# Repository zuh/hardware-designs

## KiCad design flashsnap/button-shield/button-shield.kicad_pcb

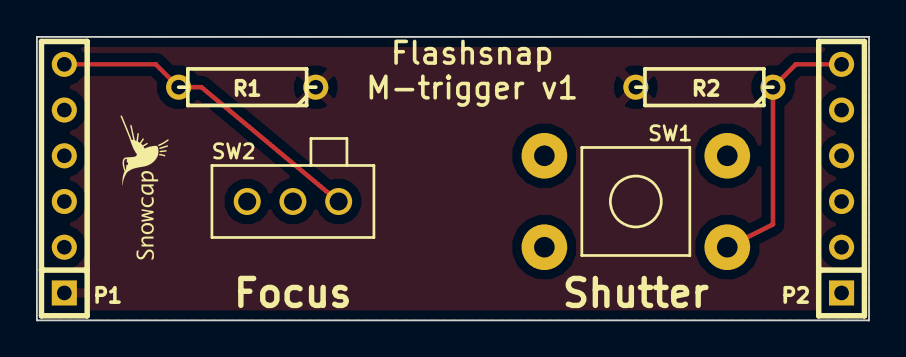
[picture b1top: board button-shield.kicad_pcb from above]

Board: 2 copper layers, 46.2 x 15.7 mm, 7 parts (0 on the bottom side), 4 nets.

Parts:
P1, P2: CONN_6; SIL-6
R1, R2: R; R3
SW1: SW_PUSH; SW_PUSH_6MM
SW2: DUAL_SWITCH_INV; SLIDE_SWITCH
VAL: REF; LOGO_SMALL_SNOWCAP_FRONT

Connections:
unnamed: P1.6, R1.2, SW2.1
unnamed: P2.6, R2.1, SW1.2
unnamed: P1.2, SW1.1, SW2.2
unnamed: P1.1, R1.1, R2.2

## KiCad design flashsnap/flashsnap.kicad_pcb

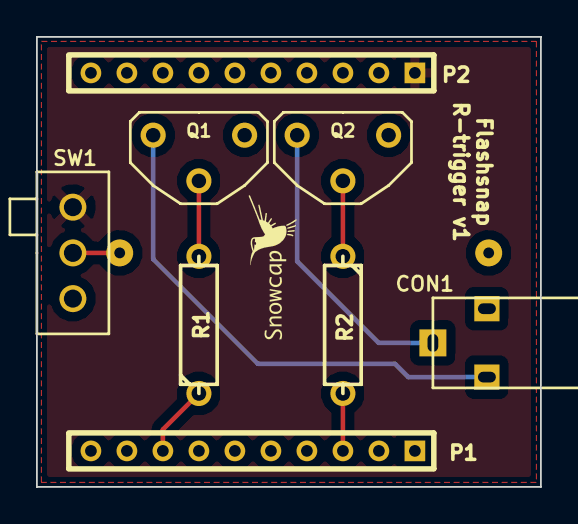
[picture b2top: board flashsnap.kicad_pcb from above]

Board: 2 copper layers, 28.0 x 25.0 mm, 10 parts (1 on the bottom side), 9 nets.

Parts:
BT1: BATTERY; BX2032
CON1: BARREL_JACK; SJ2.5PC
P1, P2: CONN_10; CONN-10-2MM
Q1, Q2: NPN; TO92PN-LARGE
R1, R2: R; R3
SW1: SWITCH_INV; SLIDE_SWITCH
VAL: REF; LOGO_SMALL_SNOWCAP_FRONT

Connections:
unnamed: P2.1, SW1.1
unnamed: BT1.2, CON1.1, P2.10, Q1.1, Q2.1
unnamed: BT1.1, SW1.2
unnamed: Q1.2, R1.2
unnamed: P1.3, R2.2
unnamed: Q2.2, R2.1
unnamed: CON1.3, Q2.3
unnamed: CON1.2, Q1.3
unnamed: P1.8, R1.1

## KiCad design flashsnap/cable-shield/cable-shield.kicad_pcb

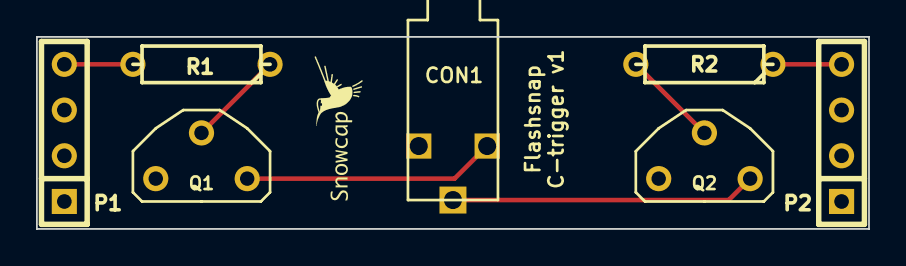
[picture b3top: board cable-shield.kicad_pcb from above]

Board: 2 copper layers, 46.2 x 10.7 mm, 8 parts (0 on the bottom side), 7 nets.

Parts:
CON1: BARREL_JACK; SJ2.5PC
P1, P2: CONN_4; SIL-4
Q1, Q2: NPN; TO92PN-LARGE
R1, R2: R; R3
VAL: REF; LOGO_SMALL_SNOWCAP_FRONT

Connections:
unnamed: CON1.1, P1.2, Q1.1, Q2.1
unnamed: CON1.2, Q1.3
unnamed: CON1.3, Q2.3
unnamed: Q2.2, R2.2
unnamed: Q1.2, R1.1
unnamed: P1.4, R1.2
unnamed: P2.4, R2.1

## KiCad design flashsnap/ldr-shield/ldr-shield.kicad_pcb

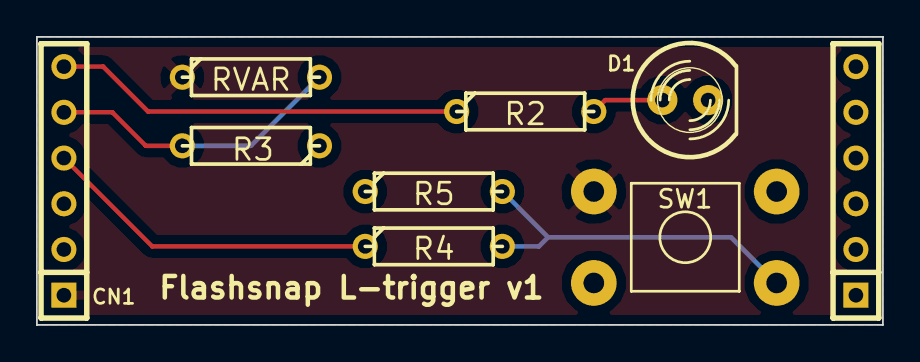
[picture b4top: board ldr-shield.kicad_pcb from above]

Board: 2 copper layers, 47.0 x 16.0 mm, 9 parts (0 on the bottom side), 7 nets.

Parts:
CN1, CN2: CN_6; SIL-6
D1: LED; LED-5MM
R1: RVAR; R3
R2, R3, R4, R5: R; R3
SW1: SW_PUSH; SW_PUSH_6MM

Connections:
unnamed: CN1.4, R4.1
unnamed: CN1.5, R1.2, R3.2
unnamed: R4.2, R5.2, SW1.2
unnamed: CN1.1, R1.1, SW1.1
unnamed: CN1.6, R2.1
unnamed: CN1.2, D1.2, R3.1, R5.1
unnamed: D1.1, R2.2

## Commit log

2014-12-04 flashsnap: Import first flashsnap designs (case)
2014-12-04 TEST
2014-12-04 TEST2
2014-12-05 flashsnap: Import first board design version
2014-12-10 flashsnap: Update main board, add manual and lightning trigger shields
2014-12-18 flashsnap: Introduce cable-shield, update others.
